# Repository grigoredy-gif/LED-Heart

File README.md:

# LED Heart

A 9 x 8 matrix of 72 red LEDs on an 85 x 50 mm board, driven by an STM8S003
microcontroller and a 74HC595 shift register. It shows a beating heart,
animations and scrolling text, and runs from three AA or AAA cells. Five buttons
choose the mode, the speed and the brightness, and switch it on and off.

| The finished board | Worn under a shirt |
|---|---|
|  |  |

| Top | Bottom |
|---|---|
|  |  |

The renders show the black solder mask the boards were ordered with. KiCad has
no 3D model of the buttons, so the renders use a look-alike of about the same size.

## Status

- **Hardware:** designed, checked and ordered at JLCPCB in November 2026
  (5 boards, assembled by JLCPCB). Built and working: all 72 LEDs and the buttons
  pass the bring-up test.
- **Firmware:** a beating heart with speed, brightness, sleep and auto-off
  (`firmware/heart`), and a bring-up test (`firmware/test`). The test and the
  display, button and sleep code have run on the board.
- **Box:** a 3D-printable box for the board and a 3 x AA holder (`enclosure/`).

## Build your own

Everything needed is in this repository.

1. **Order the boards.** Upload the three files in `fabrication/` to JLCPCB
   (Gerber zip, BOM, placement file) and follow `fabrication/READ_ME_FIRST.txt`.
   JLCPCB solders every part on the top side.
2. **Battery holder.** A 3 x AA (or AAA) holder: red wire to the + pad, black to
   the - pad on the back. 3 x 1.5 V; never more than 5 V (no 4 cells, no 9 V).
3. **Programmer.** An ST-Link V2 clone (the small USB stick, about 2 to 10 euros).
   Not a "V2-1" and not an STLINK-V3MINI: those may lack SWIM.
4. **Compiler.** SDCC 4.x (https://sdcc.sourceforge.net). Double-click
   `firmware/heart/build.bat`; it writes `led_heart.hex`.
5. **Flash.** Wire the ST-Link to J1 by the names printed on both (3.3V, SWIM,
   GND, RST; never 5 V; no cells in). Then either:
   - ST Visual Programmer (free from st.com, installs the driver), steps in
     `firmware/test/README.md`; or
   - stm8flash (https://github.com/vdudouyt/stm8flash) with the WinUSB driver
     (installed with Zadig on "STM32 STLink"): put `stm8flash.exe` in
     `firmware/tools/` and run `firmware/flash.bat`. On Windows it has to be built
     from source; leaving out the ESP-STLink part makes it build with MSYS2 gcc.
   It is worth flashing `firmware/test` first: it lights every LED in turn and
   shows each button, so a bad joint shows at once.
6. **Box.** Print `enclosure/led_heart_box.stl` open side up, no supports, and
   screw the board on with four M3 x 8 to 10 mm screws.

## How it works

[Schematic (PDF)](led_heart.pdf)

- **LED matrix.** The anodes are joined by column (9 columns), the cathodes by
  row (8 rows). Each column is driven by a microcontroller pin through a 270 ohm
  resistor; each row is switched to ground by an S8050 NPN transistor. One row
  is lit at a time: about 6.5 mA peak and 0.8 mA average per LED at 4.5 V.
- **Row select.** The 74HC595's eight outputs drive the transistor bases through
  1 kohm resistors. Its two clock inputs are tied together, so it needs only two
  microcontroller pins.
- **Microcontroller.** STM8S003F3 (TSSOP-20), all 16 I/O pins in use. It is
  programmed over SWIM with an ST-Link V2 through four pads: VDD, SWIM, GND, RST.
- **Buttons.** MODE, SPEED, DIM, BRIGHT and ON/OFF. ON/OFF is on PB5, a pin that
  can wake the chip from halt: "off" is halt with every LED dark.
- **Power.** 4.5 V from three cells, soldered to two pads on the back. An SS14
  Schottky diode protects against reversed cells. There is no regulator: the
  STM8 runs from 2.95 to 5.5 V, so keep the supply at 5 V or less (a 5 V USB
  supply works). The copper jumper JP1 can be cut to add a hard power switch.

| Signal | STM8 pins |
|---|---|
| Columns 1 to 9 | PD3, PD2, PC7, PC6, PC5, PC4, PC3, PA3, PD4 |
| 74HC595 data, clock | PD5, PD6 |
| MODE, SPEED, DIM, BRIGHT, ON/OFF | PA1, PA2, PD1 (shared with SWIM), PB4, PB5 |

## Board

- 85 x 50 mm, 2 layers, 1.6 mm, all parts on the top side, four M3 mounting holes.
- 111 parts of 9 types, all Basic or Preferred parts at JLCPCB, so economic
  assembly adds no part fees.
- Rows run on the top layer, columns on the bottom layer with one via per LED;
  ground pour on both sides.
- Five boards, all assembled, cost about 22.50 dollars at JLCPCB (November 2026,
  before shipping and VAT).

## How it was made

The schematic, the board and the order files are generated by Python scripts in
`gen/`, run with KiCad 10's own Python (pcbnew). The LED matrix and the buses are
laid by rule; the area around the chips was routed with Freerouting.

Checks before ordering:

- ERC: 0 errors, 0 warnings.
- The exported netlist compared with the intended circuit: 0 differences.
- DRC with schematic parity: 0 violations, 0 unconnected, 0 differences.
- The circuit rebuilt from the Gerber files alone: 0 shorts, 0 opens, all 72
  LEDs the right way round.
- JLCPCB's placement preview compared with the board's pin-1 positions.

The full notes (decisions, circuit, checks, bring-up steps, firmware notes) are in
[docs/design-notes.md](docs/design-notes.md).

## Files

| Path | Contents |
|---|---|
| `led_heart.kicad_pro`, `.kicad_sch`, `.kicad_pcb` | KiCad 10 project |
| `led_heart.pdf` | schematic as PDF |
| `led_heart.net` | netlist the board script reads |
| `led_heart.pretty/` | footprints of the buttons and the battery pads |
| `parts.csv` | parts with LCSC numbers and prices |
| `fabrication/` | JLCPCB order files: Gerber zip, BOM, placement file, order settings |
| `gen/` | scripts for the schematic, the board, the order files and the renders |
| `preview/` | 3D renders |
| `photos/` | photos of the finished board |
| `enclosure/` | 3D-printable box (STL, 89.6 x 54.6 x 25.1 mm): the board sits in a pocket flush with the rim, screwed onto four slim corner posts with M3 x 8 to 10 mm screws; the 3 x AA holder glued to its back rests on the floor; made by `gen/led_box.py` |
| `firmware/` | `heart/` beating heart, `test/` bring-up test (both C for SDCC), `flash.bat` for stm8flash |
| `docs/design-notes.md` | design notes |

## Rebuilding

Run the scripts in `gen/` with KiCad 10's Python while KiCad is closed. The paths
to KiCad and Freerouting 2.1.0 are set at the top of `gen/led_board.py`,
`gen/kisch.py`, `gen/frhelp.py` and `gen/build_board.sh`.

1. `led_sch.py`: schematic, ERC, netlist and PDF; `led_check.py` compares the netlist with the circuit.
2. `build_board.sh` (in Git Bash): places, routes and checks the board. Freerouting
   gives a different but equally valid routing of the chip area on every run.
3. `led_fab.py`: Gerber zip, BOM and placement file for JLCPCB, with each part's
   angle worked out from JLCPCB's own footprint.
4. `led_render.py`: the renders in `preview/`.

To order, upload the three files in `fabrication/` to JLCPCB and follow
`fabrication/READ_ME_FIRST.txt`.

## Firmware

C built with SDCC, flashed over SWIM with an ST-Link. A timer interrupt at 16 kHz
scans the rows (125 frames per second) and sets the brightness by how long each
row stays on. Speed and brightness are saved in EEPROM. ON/OFF puts the chip in
halt with the LEDs off (about 10 uA) and wakes it. The MODE button is left free
for your own animations; `firmware/heart/README.md` says how.

## License

MIT licensed, see [LICENSE](LICENSE). `gen/kisch.py` and `gen/frhelp.py` come
from my QFH receiver project.

Edy Grigore

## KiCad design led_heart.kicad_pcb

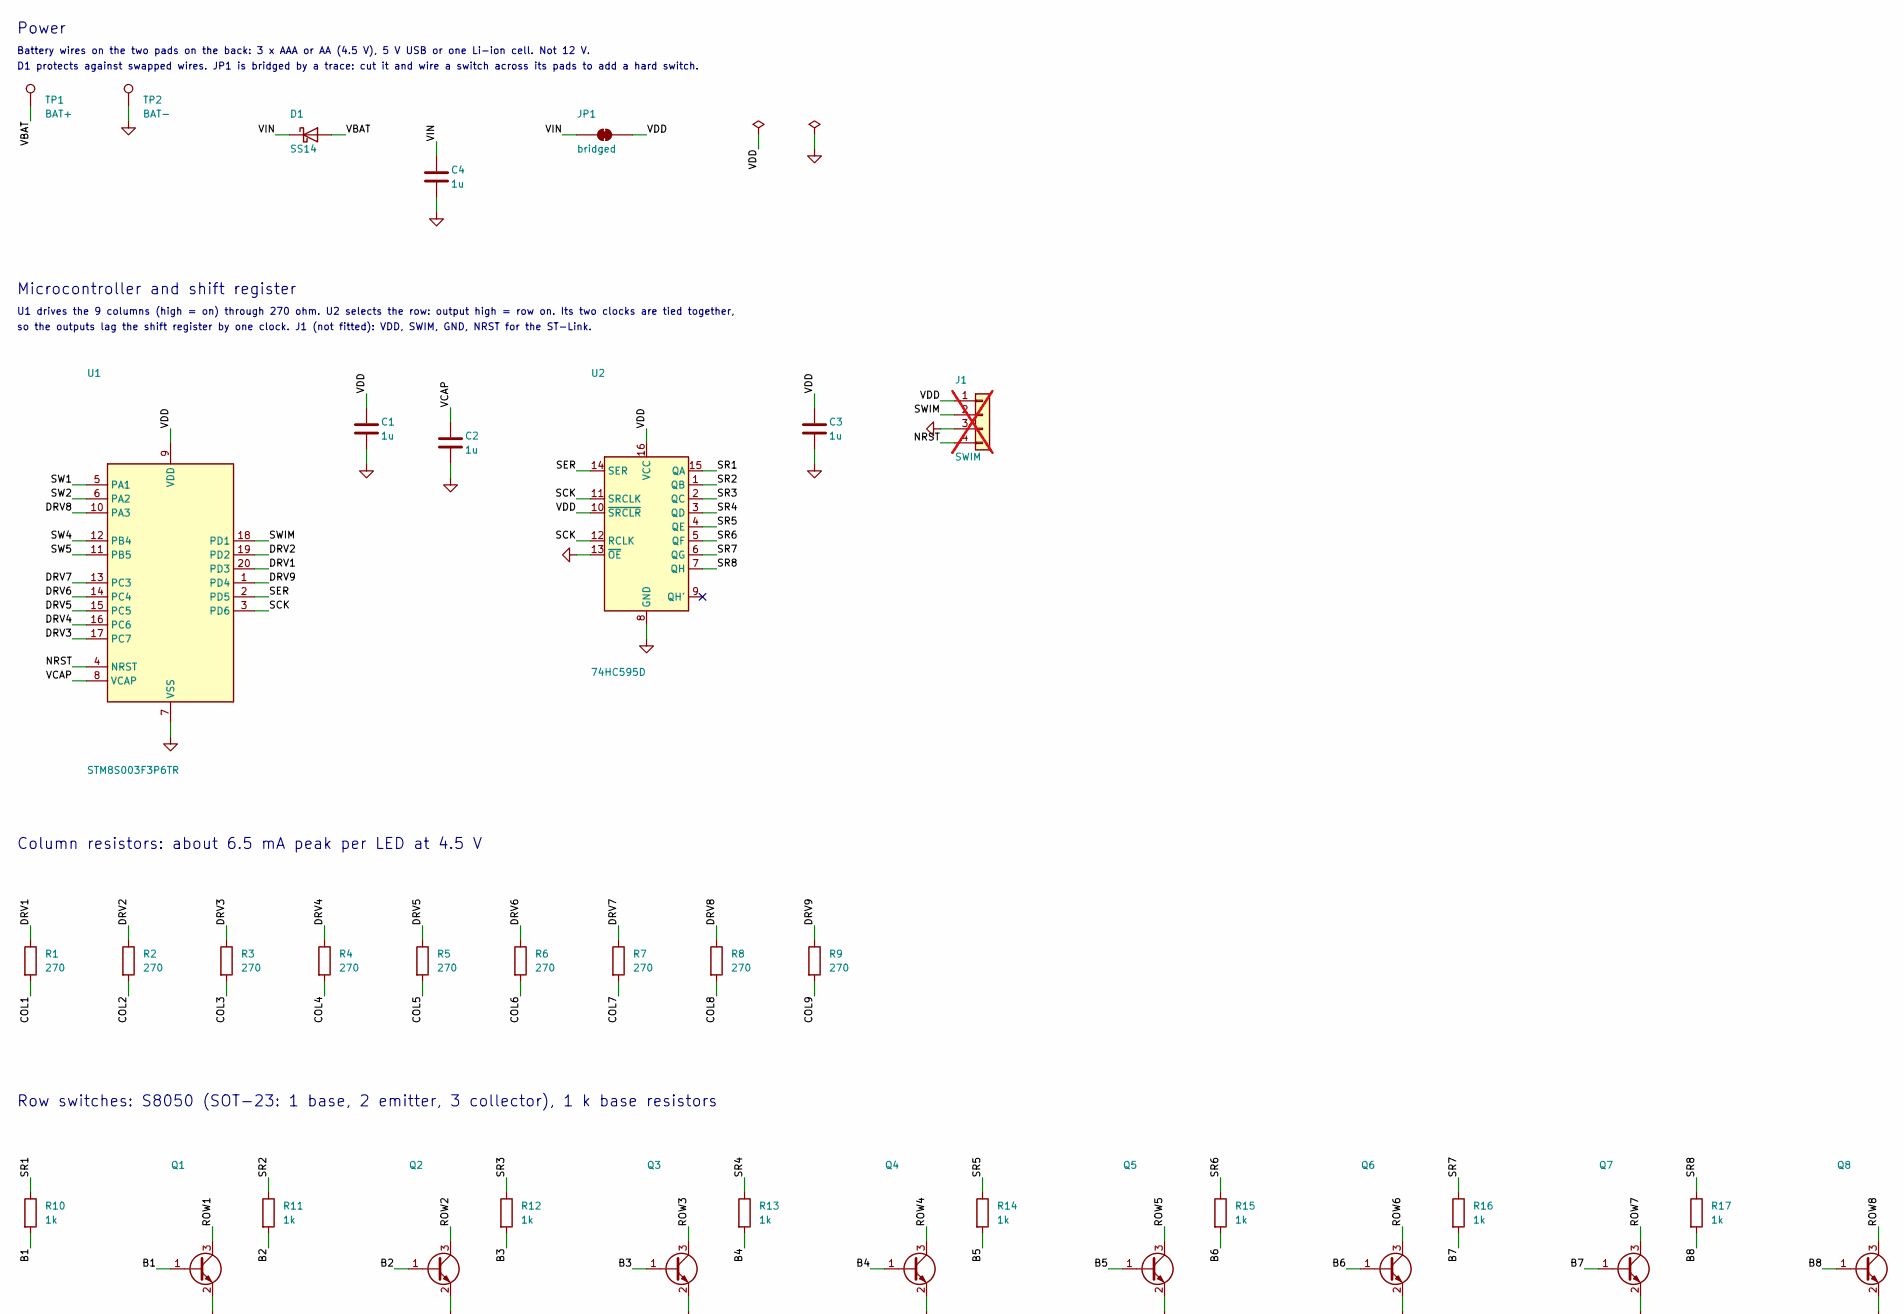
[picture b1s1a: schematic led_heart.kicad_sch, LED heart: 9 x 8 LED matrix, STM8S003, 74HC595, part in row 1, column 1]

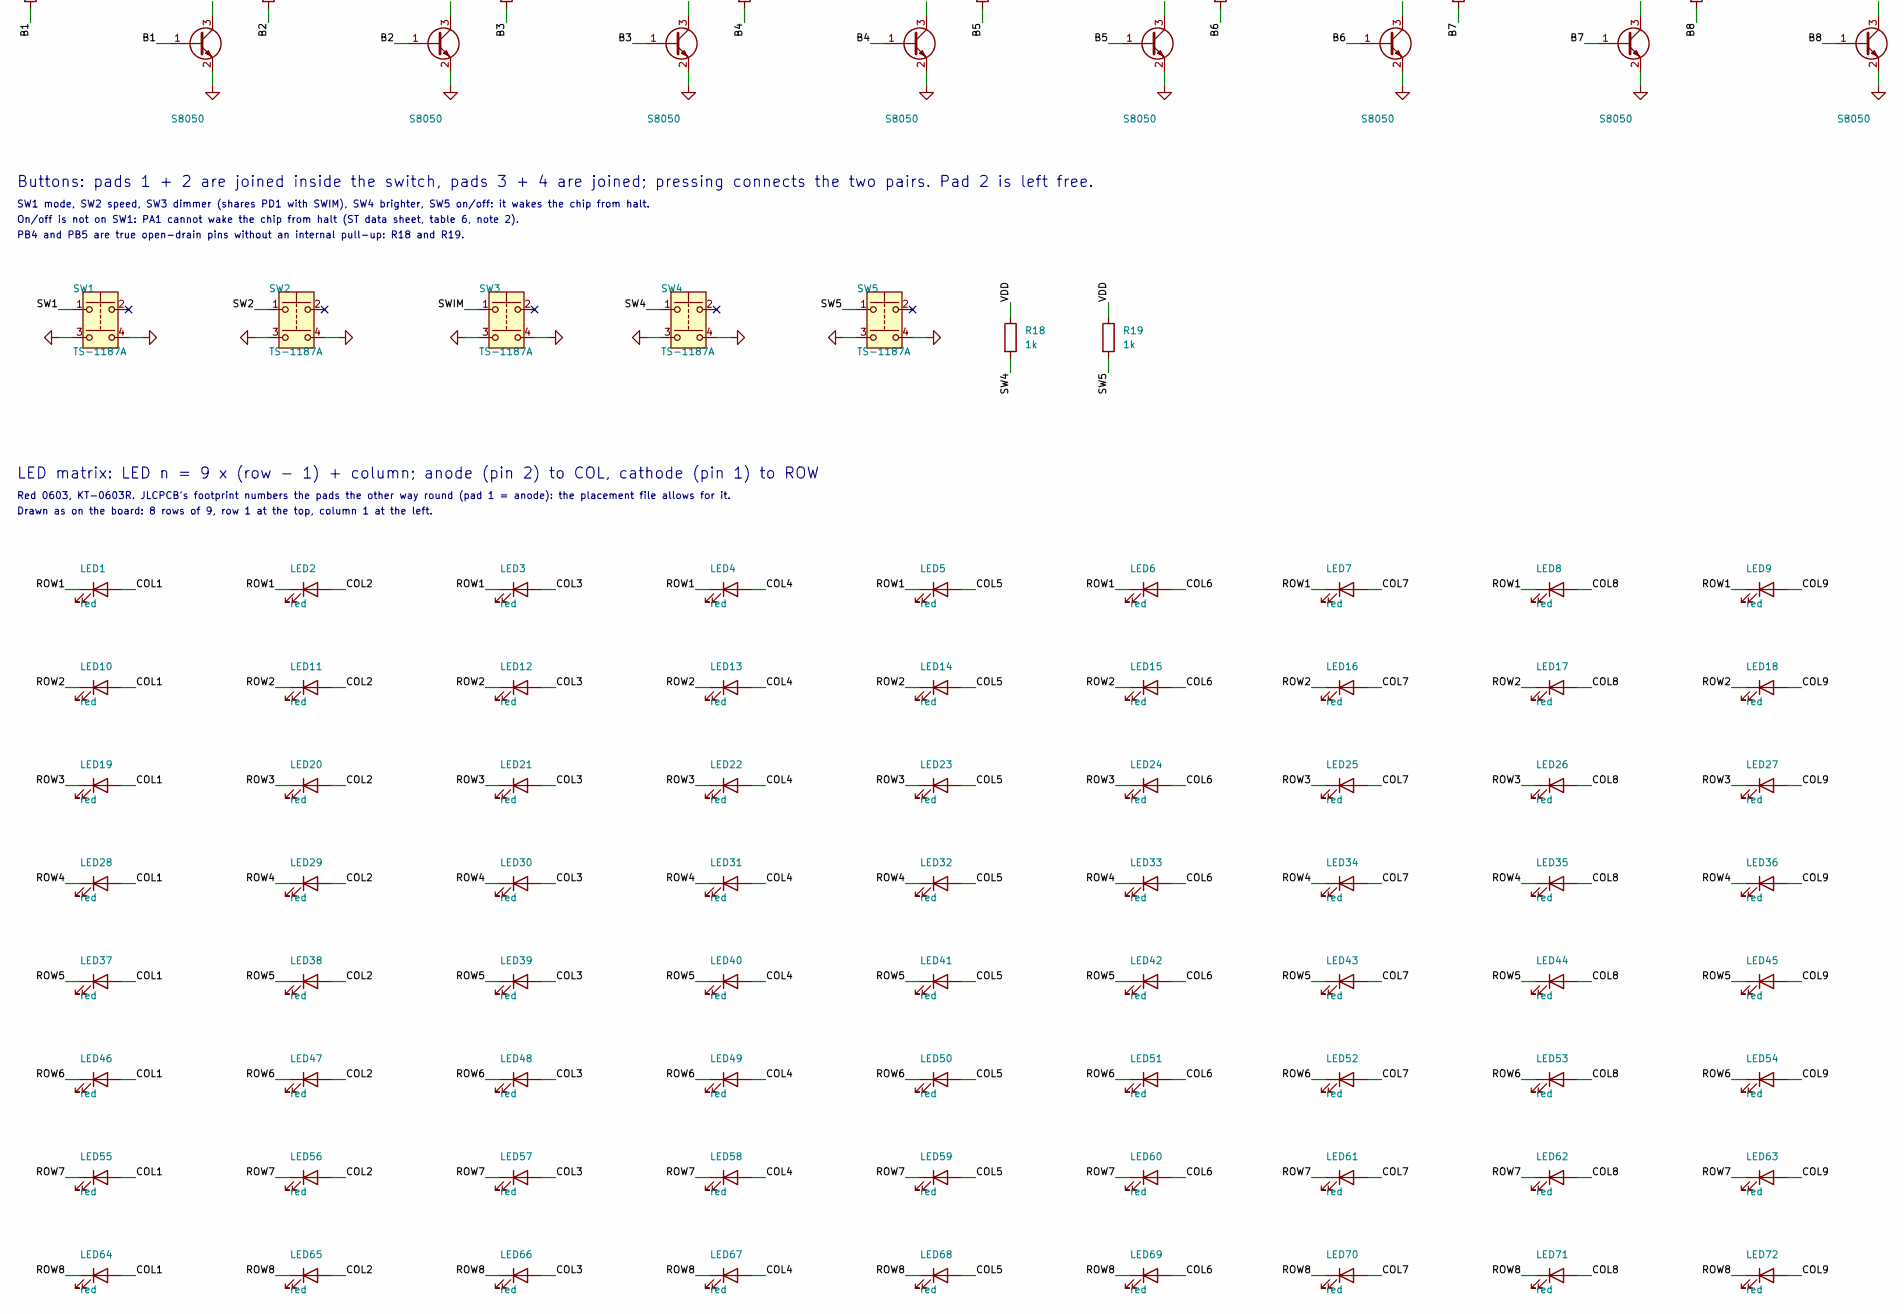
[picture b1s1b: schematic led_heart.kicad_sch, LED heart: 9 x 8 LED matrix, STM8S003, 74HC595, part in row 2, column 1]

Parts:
C1, C2, C3, C4: 1u; C_0603_1608Metric; LCSC C15849
D1: SS14; D_SMA; LCSC C2480
J1: SWIM; PinHeader_1x04_P2.54mm_Vertical; not fitted
JP1: bridged; SolderJumper-2_P1.3mm_Bridged_Pad1.0x1.5mm
LED1, LED2, LED3, LED4, LED5, LED6, LED7, LED8, LED9, LED10, LED11, LED12, LED13, LED14, LED15, LED16, LED17, LED18, LED19, LED20, LED21, LED22, LED23, LED24, LED25, LED26, LED27, LED28, LED29, LED30, LED31, LED32, LED33, LED34, LED35, LED36, LED37, LED38, LED39, LED40, LED41, LED42, LED43, LED44, LED45, LED46, LED47, LED48, LED49, LED50, LED51, LED52, LED53, LED54, LED55, LED56, LED57, LED58, LED59, LED60, LED61, LED62, LED63, LED64, LED65, LED66, LED67, LED68, LED69, LED70, LED71, LED72: red; LED_0603_1608Metric; LCSC C2286
Q1, Q2, Q3, Q4, Q5, Q6, Q7, Q8: S8050; SOT-23; LCSC C2146
R1, R2, R3, R4, R5, R6, R7, R8, R9: 270; R_0603_1608Metric; LCSC C22966
R10, R11, R12, R13, R14, R15, R16, R17, R18, R19: 1k; R_0603_1608Metric; LCSC C21190
SW1, SW2, SW3, SW4, SW5: TS-1187A; SW_TS-1187A; LCSC C318884
TP1: BAT+; BatPad_4x6
TP2: BAT-; BatPad_4x6
U1: STM8S003F3P6TR; TSSOP-20_4.4x6.5mm_P0.65mm; LCSC C52717
U2: 74HC595D; SOIC-16_3.9x9.9mm_P1.27mm; LCSC C5947

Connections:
/B1: Q1.1 (B), R10.2
/B2: Q2.1 (B), R11.2
/B3: Q3.1 (B), R12.2
/B4: Q4.1 (B), R13.2
/B5: Q5.1 (B), R14.2
/B6: Q6.1 (B), R15.2
/B7: Q7.1 (B), R16.2
/B8: Q8.1 (B), R17.2
/COL1: LED1.2 (A), LED10.2 (A), LED19.2 (A), LED28.2 (A), LED37.2 (A), LED46.2 (A), LED55.2 (A), LED64.2 (A), R1.2
/COL2: LED2.2 (A), LED11.2 (A), LED20.2 (A), LED29.2 (A), LED38.2 (A), LED47.2 (A), LED56.2 (A), LED65.2 (A), R2.2
/COL3: LED3.2 (A), LED12.2 (A), LED21.2 (A), LED30.2 (A), LED39.2 (A), LED48.2 (A), LED57.2 (A), LED66.2 (A), R3.2
/COL4: LED4.2 (A), LED13.2 (A), LED22.2 (A), LED31.2 (A), LED40.2 (A), LED49.2 (A), LED58.2 (A), LED67.2 (A), R4.2
/COL5: LED5.2 (A), LED14.2 (A), LED23.2 (A), LED32.2 (A), LED41.2 (A), LED50.2 (A), LED59.2 (A), LED68.2 (A), R5.2
/COL6: LED6.2 (A), LED15.2 (A), LED24.2 (A), LED33.2 (A), LED42.2 (A), LED51.2 (A), LED60.2 (A), LED69.2 (A), R6.2
/COL7: LED7.2 (A), LED16.2 (A), LED25.2 (A), LED34.2 (A), LED43.2 (A), LED52.2 (A), LED61.2 (A), LED70.2 (A), R7.2
/COL8: LED8.2 (A), LED17.2 (A), LED26.2 (A), LED35.2 (A), LED44.2 (A), LED53.2 (A), LED62.2 (A), LED71.2 (A), R8.2
/COL9: LED9.2 (A), LED18.2 (A), LED27.2 (A), LED36.2 (A), LED45.2 (A), LED54.2 (A), LED63.2 (A), LED72.2 (A), R9.2
/DRV1: R1.1, U1.20 (PD3)
/DRV2: R2.1, U1.19 (PD2)
/DRV3: R3.1, U1.17 (PC7)
/DRV4: R4.1, U1.16 (PC6)
/DRV5: R5.1, U1.15 (PC5)
/DRV6: R6.1, U1.14 (PC4)
/DRV7: R7.1, U1.13 (PC3)
/DRV8: R8.1, U1.10 (PA3)
/DRV9: R9.1, U1.1 (PD4)
/NRST: J1.4, U1.4 (NRST)
/ROW1: LED1.1 (K), LED2.1 (K), LED3.1 (K), LED4.1 (K), LED5.1 (K), LED6.1 (K), LED7.1 (K), LED8.1 (K), LED9.1 (K), Q1.3 (C)
/ROW2: LED10.1 (K), LED11.1 (K), LED12.1 (K), LED13.1 (K), LED14.1 (K), LED15.1 (K), LED16.1 (K), LED17.1 (K), LED18.1 (K), Q2.3 (C)
/ROW3: LED19.1 (K), LED20.1 (K), LED21.1 (K), LED22.1 (K), LED23.1 (K), LED24.1 (K), LED25.1 (K), LED26.1 (K), LED27.1 (K), Q3.3 (C)
/ROW4: LED28.1 (K), LED29.1 (K), LED30.1 (K), LED31.1 (K), LED32.1 (K), LED33.1 (K), LED34.1 (K), LED35.1 (K), LED36.1 (K), Q4.3 (C)
/ROW5: LED37.1 (K), LED38.1 (K), LED39.1 (K), LED40.1 (K), LED41.1 (K), LED42.1 (K), LED43.1 (K), LED44.1 (K), LED45.1 (K), Q5.3 (C)
/ROW6: LED46.1 (K), LED47.1 (K), LED48.1 (K), LED49.1 (K), LED50.1 (K), LED51.1 (K), LED52.1 (K), LED53.1 (K), LED54.1 (K), Q6.3 (C)
/ROW7: LED55.1 (K), LED56.1 (K), LED57.1 (K), LED58.1 (K), LED59.1 (K), LED60.1 (K), LED61.1 (K), LED62.1 (K), LED63.1 (K), Q7.3 (C)
/ROW8: LED64.1 (K), LED65.1 (K), LED66.1 (K), LED67.1 (K), LED68.1 (K), LED69.1 (K), LED70.1 (K), LED71.1 (K), LED72.1 (K), Q8.3 (C)
/SCK: U1.3 (PD6), U2.11 (SRCLK), U2.12 (RCLK)
/SER: U1.2 (PD5), U2.14 (SER)
/SR1: R10.1, U2.15 (QA)
/SR2: R11.1, U2.1 (QB)
/SR3: R12.1, U2.2 (QC)
/SR4: R13.1, U2.3 (QD)
/SR5: R14.1, U2.4 (QE)
/SR6: R15.1, U2.5 (QF)
/SR7: R16.1, U2.6 (QG)
/SR8: R17.1, U2.7 (QH)
/SW1: SW1.1, U1.5 (PA1)
/SW2: SW2.1, U1.6 (PA2)
/SW4: R18.2, SW4.1, U1.12 (PB4)
/SW5: R19.2, SW5.1, U1.11 (PB5)
/SWIM: J1.2, SW3.1, U1.18 (PD1)
/VBAT: D1.2 (A), TP1.1
/VCAP: C2.1, U1.8 (VCAP)
/VDD: C1.1, C3.1, J1.1, JP1.2 (B), R18.1, R19.1, U1.9 (VDD), U2.10 (~SRCLR), U2.16 (VCC)
/VIN: C4.1, D1.1 (K), JP1.1 (A)
GND: C1.2, C2.2, C3.2, C4.2, J1.3, Q1.2 (E), Q2.2 (E), Q3.2 (E), Q4.2 (E), Q5.2 (E), Q6.2 (E), Q7.2 (E), Q8.2 (E), SW1.3, SW1.4, SW2.3, SW2.4, SW3.3, SW3.4, SW4.3, SW4.4, SW5.3, SW5.4, TP2.1, U1.7 (VSS), U2.8 (GND), U2.13 (~OE)

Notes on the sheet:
Power
Battery wires on the two pads on the back: 3 x AAA or AA (4.5 V), 5 V USB or one Li-ion cell. Not 12 V.
D1 protects against swapped wires. JP1 is bridged by a trace: cut it and wire a switch across its pads to add a hard switch.
Microcontroller and shift register
U1 drives the 9 columns (high = on) through 270 ohm. U2 selects the row: output high = row on. Its two clocks are tied together,
so the outputs lag the shift register by one clock. J1 (not fitted): VDD, SWIM, GND, NRST for the ST-Link.
Column resistors: about 6.5 mA peak per LED at 4.5 V
Row switches: S8050 (SOT-23: 1 base, 2 emitter, 3 collector), 1 k base resistors
Buttons: pads 1 + 2 are joined inside the switch, pads 3 + 4 are joined; pressing connects the two pairs. Pad 2 is left free.
SW1 mode, SW2 speed, SW3 dimmer (shares PD1 with SWIM), SW4 brighter, SW5 on/off: it wakes the chip from halt.
On/off is not on SW1: PA1 cannot wake the chip from halt (ST data sheet, table 6, note 2).
PB4 and PB5 are true open-drain pins without an internal pull-up: R18 and R19.
LED matrix: LED n = 9 x (row - 1) + column; anode (pin 2) to COL, cathode (pin 1) to ROW
Red 0603, KT-0603R. JLCPCB's footprint numbers the pads the other way round (pad 1 = anode): the placement file allows for it.
Drawn as on the board: 8 rows of 9, row 1 at the top, column 1 at the left.

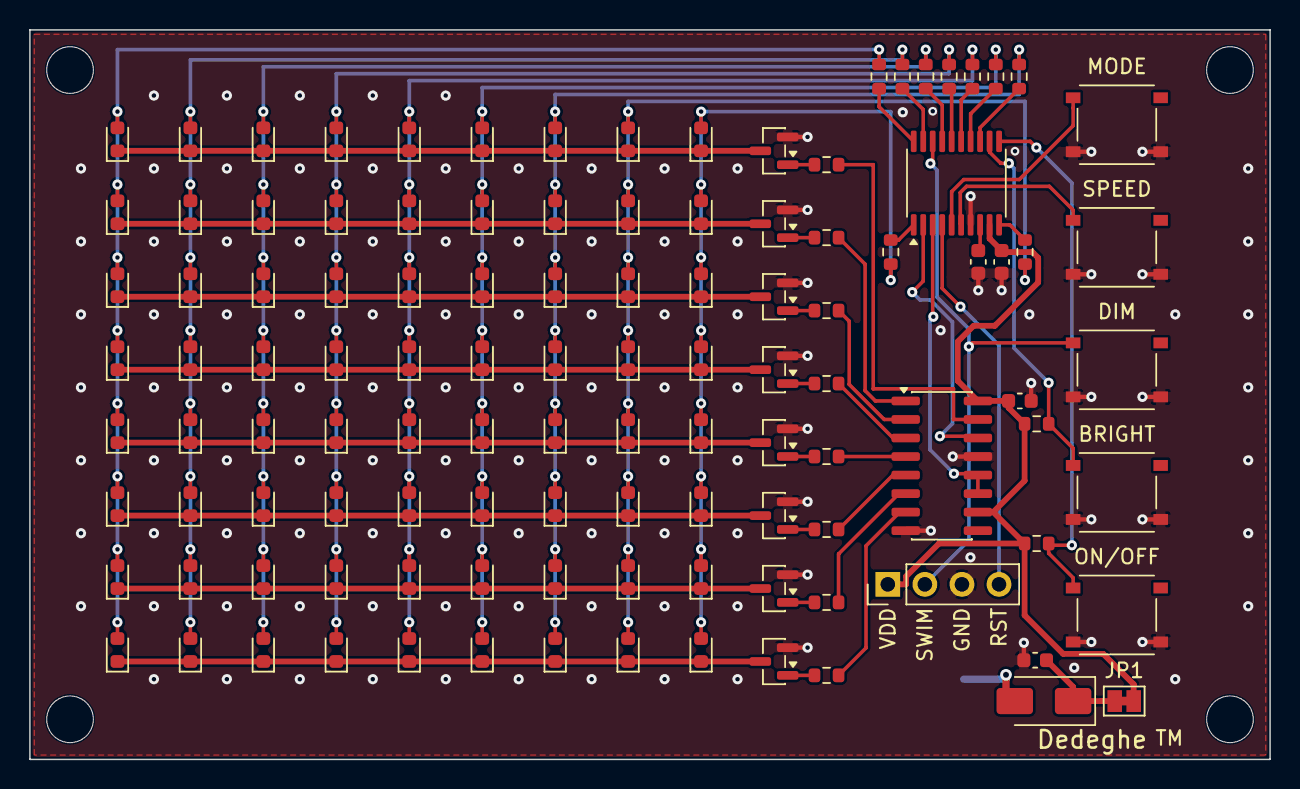
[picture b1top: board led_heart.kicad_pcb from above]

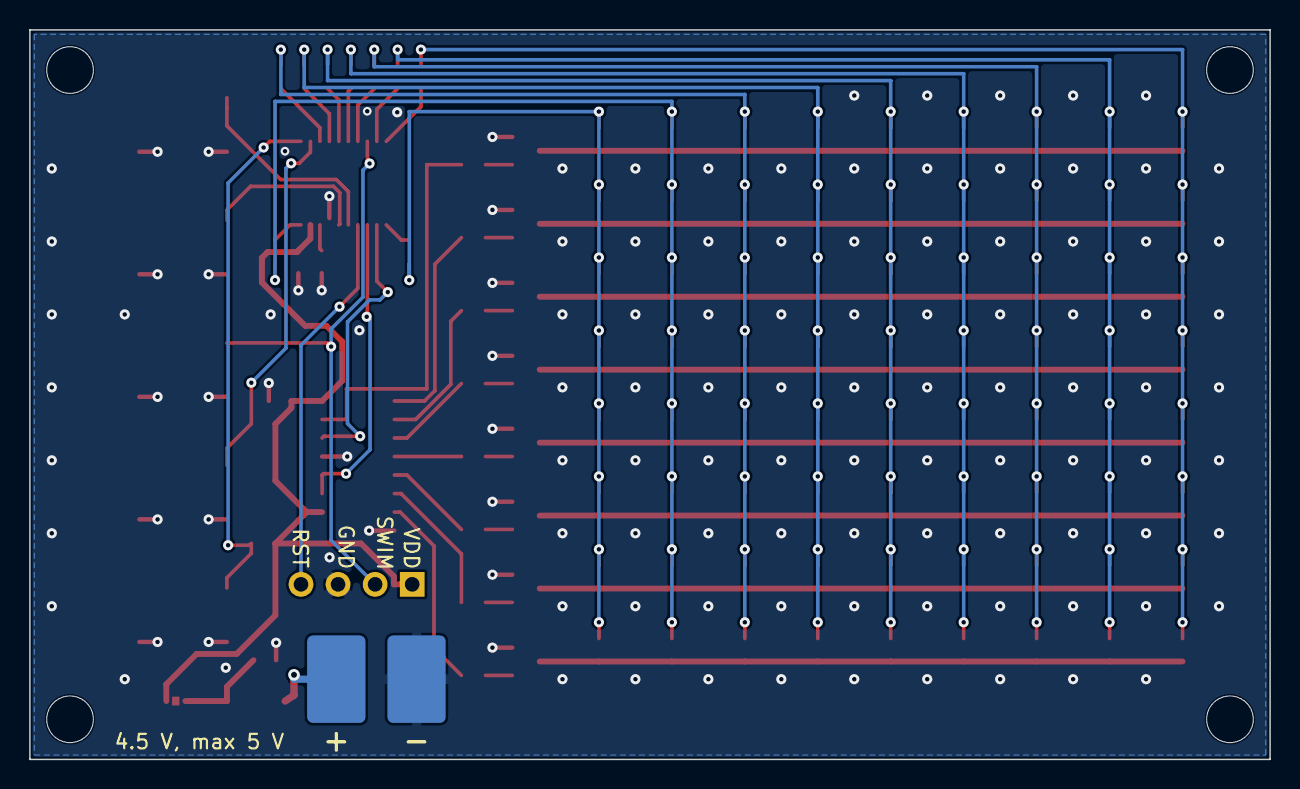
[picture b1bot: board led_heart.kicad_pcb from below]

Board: 2 copper layers, 85.0 x 50.0 mm, 119 parts (2 on the bottom side), 55 nets.

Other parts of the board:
H1, H2, H3, H4: M3; MountingHole_3.2mm_M3

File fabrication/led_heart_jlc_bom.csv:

Comment,Designator,Footprint,LCSC Part #
1u,"C1,C2,C3,C4",C_0603_1608Metric,C15849
SS14,D1,D_SMA,C2480
red,"LED1,LED2,LED3,LED4,LED5,LED6,LED7,LED8,LED9,LED10,LED11,LED12,LED13,LED14,LED15,LED16,LED17,LED18,LED19,LED20,LED21,LED22,LED23,LED24,LED25,LED26,LED27,LED28,LED29,LED30,LED31,LED32,LED33,LED34,LED35,LED36,LED37,LED38,LED39,LED40,LED41,LED42,LED43,LED44,LED45,LED46,LED47,LED48,LED49,LED50,LED51,LED52,LED53,LED54,LED55,LED56,LED57,LED58,LED59,LED60,LED61,LED62,LED63,LED64,LED65,LED66,LED67,LED68,LED69,LED70,LED71,LED72",LED_0603_1608Metric,C2286
S8050,"Q1,Q2,Q3,Q4,Q5,Q6,Q7,Q8",SOT-23,C2146
270,"R1,R2,R3,R4,R5,R6,R7,R8,R9",R_0603_1608Metric,C22966
1k,"R10,R11,R12,R13,R14,R15,R16,R17,R18,R19",R_0603_1608Metric,C21190
TS-1187A,"SW1,SW2,SW3,SW4,SW5",SW_TS-1187A,C318884
STM8S003F3P6TR,U1,TSSOP-20_4.4x6.5mm_P0.65mm,C52717
74HC595D,U2,SOIC-16_3.9x9.9mm_P1.27mm,C5947

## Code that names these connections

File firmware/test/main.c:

/*
 * LED heart board: bring-up test (STM8S003F3, SDCC)
 *
 * What it does, over and over:
 *   1. lights the 72 LEDs one at a time, row by row from the top left
 *      (0.2 s each, about 15 s in all);
 *   2. lights every LED for 2 s;
 *   3. shows the heart for 3 s.
 * While MODE, SPEED, BRIGHT or ON/OFF is held, the whole column 1, 2, 4 or 5
 * lights instead (DIM is not read: its pin is the programming pin SWIM, and
 * this test leaves SWIM working so the board can always be flashed again).
 *
 * Reading the result: a dark dot = that LED or its joint; a dark row = its
 * transistor, base resistor or the 595; a dark column = its 270 ohm resistor
 * or the STM8 pin; two dots lit at once = a solder bridge.
 *
 * Circuit (docs/design-notes.md, "Circuit"):
 *   columns 1..9 (anodes, high = on): PD3 PD2 PC7 PC6 PC5 PC4 PC3 PA3 PD4
 *   rows 1..8 (cathodes): S8050 driven by 74HC595 QA..QH, high = on
 *   595: SER = PD5, SRCLK and RCLK tied = PD6, OE low, SRCLR high
 *   buttons (low = pressed): MODE PA1, SPEED PA2, DIM PD1, BRIGHT PB4, ON/OFF PB5
 */
#include <stdint.h>

#define REG(a) (*(volatile uint8_t *)(a))

#define PA_ODR REG(0x5000)
#define PA_IDR REG(0x5001)
#define PA_DDR REG(0x5002)
#define PA_CR1 REG(0x5003)
#define PA_CR2 REG(0x5004)
#define PB_IDR REG(0x5006)
#define PC_ODR REG(0x500A)
#define PC_DDR REG(0x500C)
#define PC_CR1 REG(0x500D)
#define PD_ODR REG(0x500F)
#define PD_DDR REG(0x5011)
#define PD_CR1 REG(0x5012)
#define PD_CR2 REG(0x5013)
#define CLK_CKDIVR REG(0x50C6)
#define TIM4_CR1 REG(0x5340)
#define TIM4_IER REG(0x5343)
#define TIM4_SR REG(0x5344)
#define TIM4_PSCR REG(0x5347)
#define TIM4_ARR REG(0x5348)

/* column pins on each port */
#define PA_COLS 0x08 /* PA3 */
#define PC_COLS 0xF8 /* PC3..PC7 */
#define PD_COLS 0x1C /* PD2, PD3, PD4 */
#define SER 0x20     /* PD5 */
#define SCK 0x40     /* PD6 */

/* one 9-bit word per row, bit 0 = column 1 (left) */
static volatile uint16_t fb[8];
static volatile uint8_t held_col; /* 0 = no button held, else column to light */
static volatile uint16_t ms;
static uint8_t row; /* row the next tick shows, 0 = top */

static const uint16_t heart[8] = {
    /* .##...##.  ####.####  #########  #########
       .#######.  ..#####..  ...###...  ....#.... */
    0x0C6, 0x1EF, 0x1FF, 0x1FF, 0x0FE, 0x07C, 0x038, 0x010};

static void short_wait(void) /* about 2.5 us at 16 MHz */
{
    uint8_t i;
    for (i = 0; i < 10; i++)
        __asm__("nop");
}

/* One clock of the 595. The two clocks are tied, so the outputs show what the
   shift register held before this clock. SER and SCK change in separate
   writes. */
static void clock595(uint8_t ser)
{
    if (ser)
        PD_ODR |= SER;
    else
        PD_ODR &= (uint8_t)~SER;
    PD_ODR |= SCK;
    __asm__("nop");
    __asm__("nop");
    PD_ODR &= (uint8_t)~SCK;
}

static void columns_off(void)
{
    PA_ODR &= (uint8_t)~PA_COLS;
    PC_ODR &= (uint8_t)~PC_COLS;
    PD_ODR &= (uint8_t)~PD_COLS;
}

static void columns_on(uint16_t b)
{
    uint8_t a = 0, c = 0, d = 0;
    if (b & 0x001) d |= 0x08; /* col 1 PD3 */
    if (b & 0x002) d |= 0x04; /* col 2 PD2 */
    if (b & 0x004) c |= 0x80; /* col 3 PC7 */
    if (b & 0x008) c |= 0x40; /* col 4 PC6 */
    if (b & 0x010) c |= 0x20; /* col 5 PC5 */
    if (b & 0x020) c |= 0x10; /* col 6 PC4 */
    if (b & 0x040) c |= 0x08; /* col 7 PC3 */
    if (b & 0x080) a |= 0x08; /* col 8 PA3 */
    if (b & 0x100) d |= 0x10; /* col 9 PD4 */
    PA_ODR |= a;
    PC_ODR |= c;
    PD_ODR |= d;
}

/* 1 ms tick: next row. 8 rows -> 125 frames per second. */
void tim4_isr(void) __interrupt(23)
{
    uint16_t b;
    TIM4_SR = 0;
    columns_off();
    /* the clock that brings up row 8 feeds the next 1 in, for row 1 */
    clock595(row == 7);
    short_wait(); /* let the old row's transistor switch off */
    b = held_col ? (uint16_t)(1u << (held_col - 1)) : fb[row];
    columns_on(b);
    row = (row + 1) & 7;
    ms++;
}

static uint16_t now(void)
{
    uint16_t t;
    __asm__("sim");
    t = ms;
    __asm__("rim");
    return t;
}

static void read_buttons(void)
{
    uint8_t col = 0;
    if (!(PA_IDR & 0x02)) col = 1;      /* MODE   PA1 */
    else if (!(PA_IDR & 0x04)) col = 2; /* SPEED  PA2 */
    else if (!(PB_IDR & 0x10)) col = 4; /* BRIGHT PB4 */
    else if (!(PB_IDR & 0x20)) col = 5; /* ON/OFF PB5 */
    held_col = col;
}

static void wait_ms(uint16_t n)
{
    uint16_t start = now();
    while ((uint16_t)(now() - start) < n)
        read_buttons();
}

static void show(const uint16_t *p)
{
    uint8_t r;
    for (r = 0; r < 8; r++)
        fb[r] = p ? p[r] : 0;
}

void main(void)
{
    uint8_t r, c;

    CLK_CKDIVR = 0; /* 16 MHz */

    /* 595 lines first: outputs, low, fast */
    PD_ODR &= (uint8_t)~(SER | SCK);
    PD_DDR |= SER | SCK;
    PD_CR1 |= SER | SCK;
    PD_CR2 |= SER | SCK;

    /* clear the 595 (9 clocks with SER low), then put one 1 in for row 1 */
    for (c = 0; c < 9; c++)
        clock595(0);
    clock595(1);
    row = 0;

    /* only now the columns: push-pull outputs, low */
    columns_off();
    PA_DDR |= PA_COLS;
    PA_CR1 |= PA_COLS;
    PC_DDR |= PC_COLS;
    PC_CR1 |= PC_COLS;
    PD_DDR |= PD_COLS;
    PD_CR1 |= PD_COLS;

    /* buttons: PA1, PA2 inputs with pull-up; PB4, PB5 have R18, R19 */
    PA_CR1 |= 0x06;

    /* TIM4: 16 MHz / 64 / 250 = 1 kHz */
    TIM4_PSCR = 6;
    TIM4_ARR = 249;
    TIM4_SR = 0;
    TIM4_IER = 1;
    TIM4_CR1 = 1;
    __asm__("rim");

    for (;;) {
        /* 1. one LED at a time */
        for (r = 0; r < 8; r++) {
            for (c = 0; c < 9; c++) {
                show(0);
                fb[r] = (uint16_t)(1u << c);
                wait_ms(200);
            }
        }
        /* 2. all on */
        for (r = 0; r < 8; r++)
            fb[r] = 0x1FF;
        wait_ms(2000);
        /* 3. heart */
        show(heart);
        wait_ms(3000);
    }
}
